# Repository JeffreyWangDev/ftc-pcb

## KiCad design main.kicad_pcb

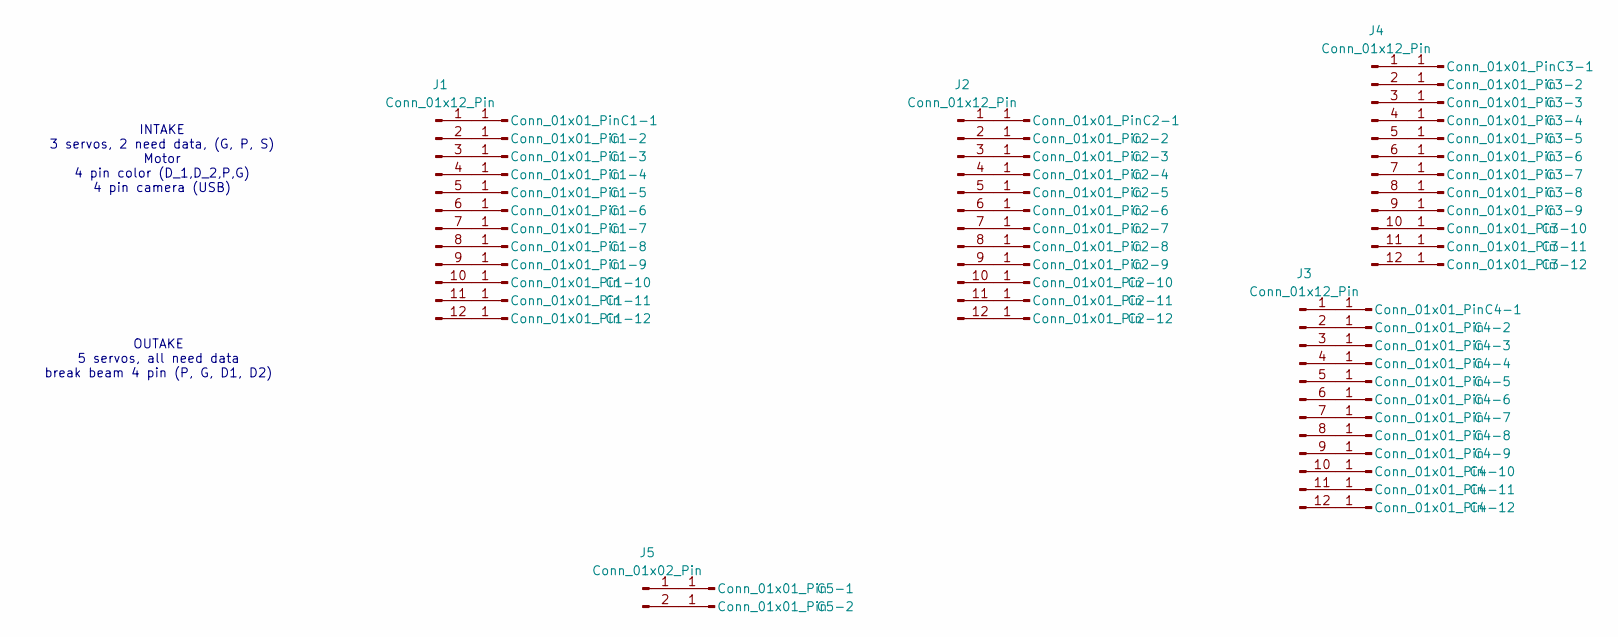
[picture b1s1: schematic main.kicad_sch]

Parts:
C1-1, C1-2, C1-3, C1-4, C1-5, C1-6, C1-7, C1-8, C1-9, C1-10, C1-11, C1-12, C2-1, C2-2, C2-3, C2-4, C2-5, C2-6, C2-7, C2-8, C2-9, C2-10, C2-11, C2-12, C3-1, C3-2, C3-3, C3-4, C3-5, C3-6, C3-7, C3-8, C3-9, C3-10, C3-11, C3-12, C4-1, C4-2, C4-3, C4-4, C4-5, C4-6, C4-7, C4-8, C4-9, C4-10, C4-11, C4-12: Conn_01x01_Pin; SolderWire-0.75sqmm_1x01_D1.25mm_OD2.3mm
C5-1, C5-2: Conn_01x01_Pin; SolderWire-1sqmm_1x01_D1.4mm_OD2.7mm
J1, J2, J3, J4: Conn_01x12_Pin; JST_XH_B12B-XH-A_1x12_P2.50mm_Vertical
J5: Conn_01x02_Pin; JST_VH_B2P-VH-B_1x02_P3.96mm_Vertical

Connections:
unnamed: C1-1.1, J1.1
unnamed: C1-2.1, J1.2
unnamed: C1-3.1, J1.3
unnamed: C1-4.1, J1.4
unnamed: C1-5.1, J1.5
unnamed: C1-6.1, J1.6
unnamed: C1-7.1, J1.7
unnamed: C1-8.1, J1.8
unnamed: C1-9.1, J1.9
unnamed: C1-10.1, J1.10
unnamed: C1-11.1, J1.11
unnamed: C1-12.1, J1.12
unnamed: C2-1.1, J2.1
unnamed: C2-2.1, J2.2
unnamed: C2-3.1, J2.3
unnamed: C2-4.1, J2.4
unnamed: C2-5.1, J2.5
unnamed: C2-6.1, J2.6
unnamed: C2-7.1, J2.7
unnamed: C2-8.1, J2.8
unnamed: C2-9.1, J2.9
unnamed: C2-10.1, J2.10
unnamed: C2-11.1, J2.11
unnamed: C2-12.1, J2.12
unnamed: C3-1.1, J4.1
unnamed: C3-2.1, J4.2
unnamed: C3-3.1, J4.3
unnamed: C3-4.1, J4.4
unnamed: C3-5.1, J4.5
unnamed: C3-6.1, J4.6
unnamed: C3-7.1, J4.7
unnamed: C3-8.1, J4.8
unnamed: C3-9.1, J4.9
unnamed: C3-10.1, J4.10
unnamed: C3-11.1, J4.11
unnamed: C3-12.1, J4.12
unnamed: C4-1.1, J3.1
unnamed: C4-2.1, J3.2
unnamed: C4-3.1, J3.3
unnamed: C4-4.1, J3.4
unnamed: C4-5.1, J3.5
unnamed: C4-6.1, J3.6
unnamed: C4-7.1, J3.7
unnamed: C4-8.1, J3.8
unnamed: C4-9.1, J3.9
unnamed: C4-10.1, J3.10
unnamed: C4-11.1, J3.11
unnamed: C4-12.1, J3.12
unnamed: C5-1.1, J5.1
unnamed: C5-2.1, J5.2

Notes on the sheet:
OUTAKE 5 servos, all need data break beam 4 pin (P, G, D1, D2)
INTAKE 3 servos, 2 need data, (G, P, S) Motor 4 pin color (D_1,D_2,P,G) 4 pin camera (USB)

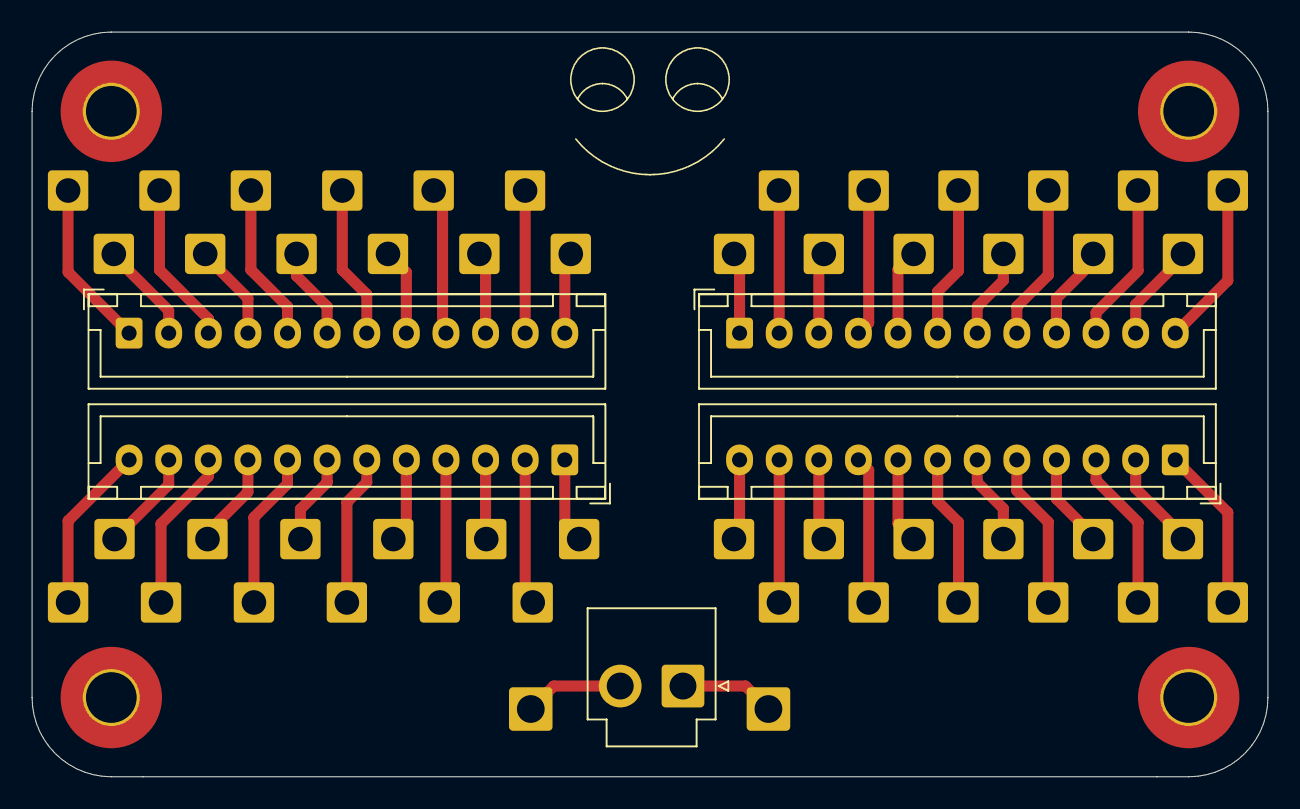
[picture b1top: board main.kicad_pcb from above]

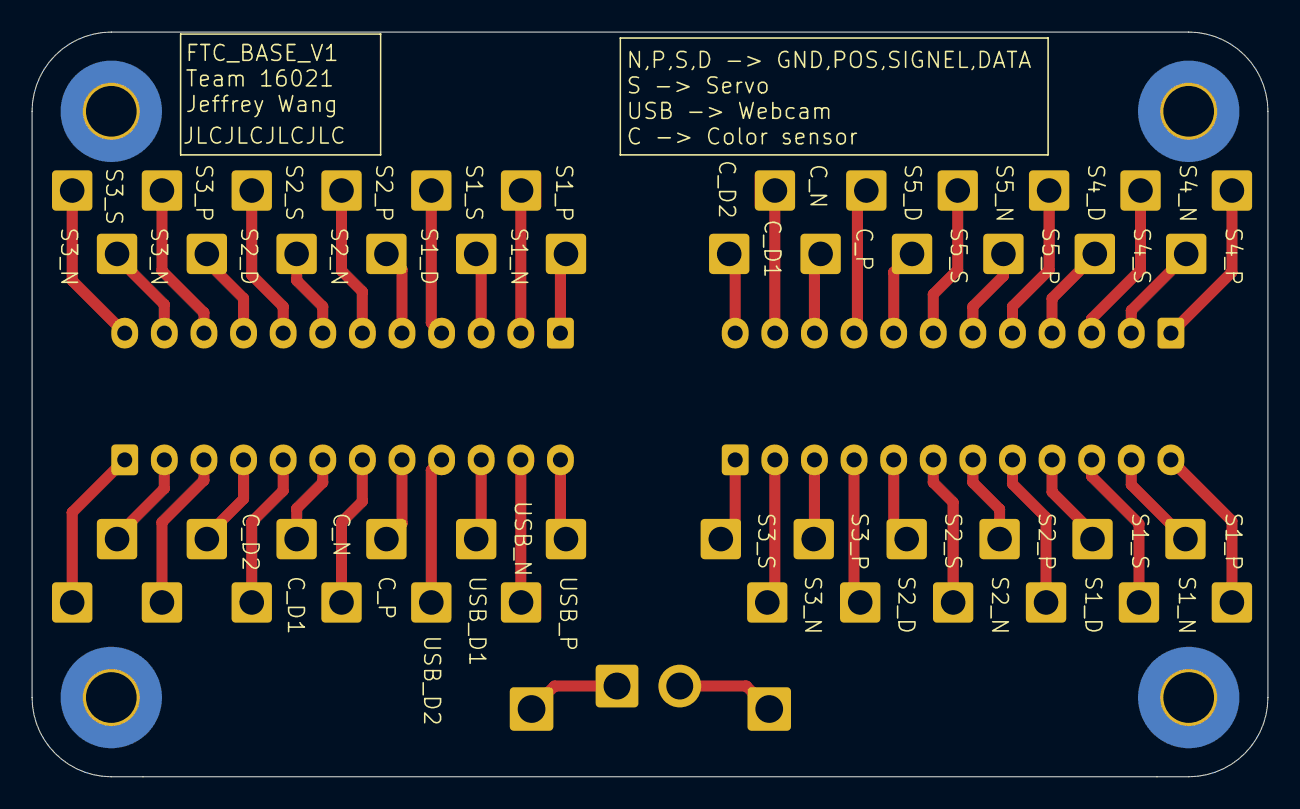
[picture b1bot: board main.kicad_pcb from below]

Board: 2 copper layers, 78.0 x 47.0 mm, 55 parts (50 on the bottom side), 50 nets.

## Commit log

2025-01-03 init
2025-01-05 new number
2025-01-05 new for rick
